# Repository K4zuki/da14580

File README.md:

# da14580
DA14580/murata module PCBs

<br />This work is licensed under a <a rel="license" href="http://creativecommons.org/licenses/by-sa/4.0/">Creative Commons Attribution-ShareAlike 4.0 International License</a>.

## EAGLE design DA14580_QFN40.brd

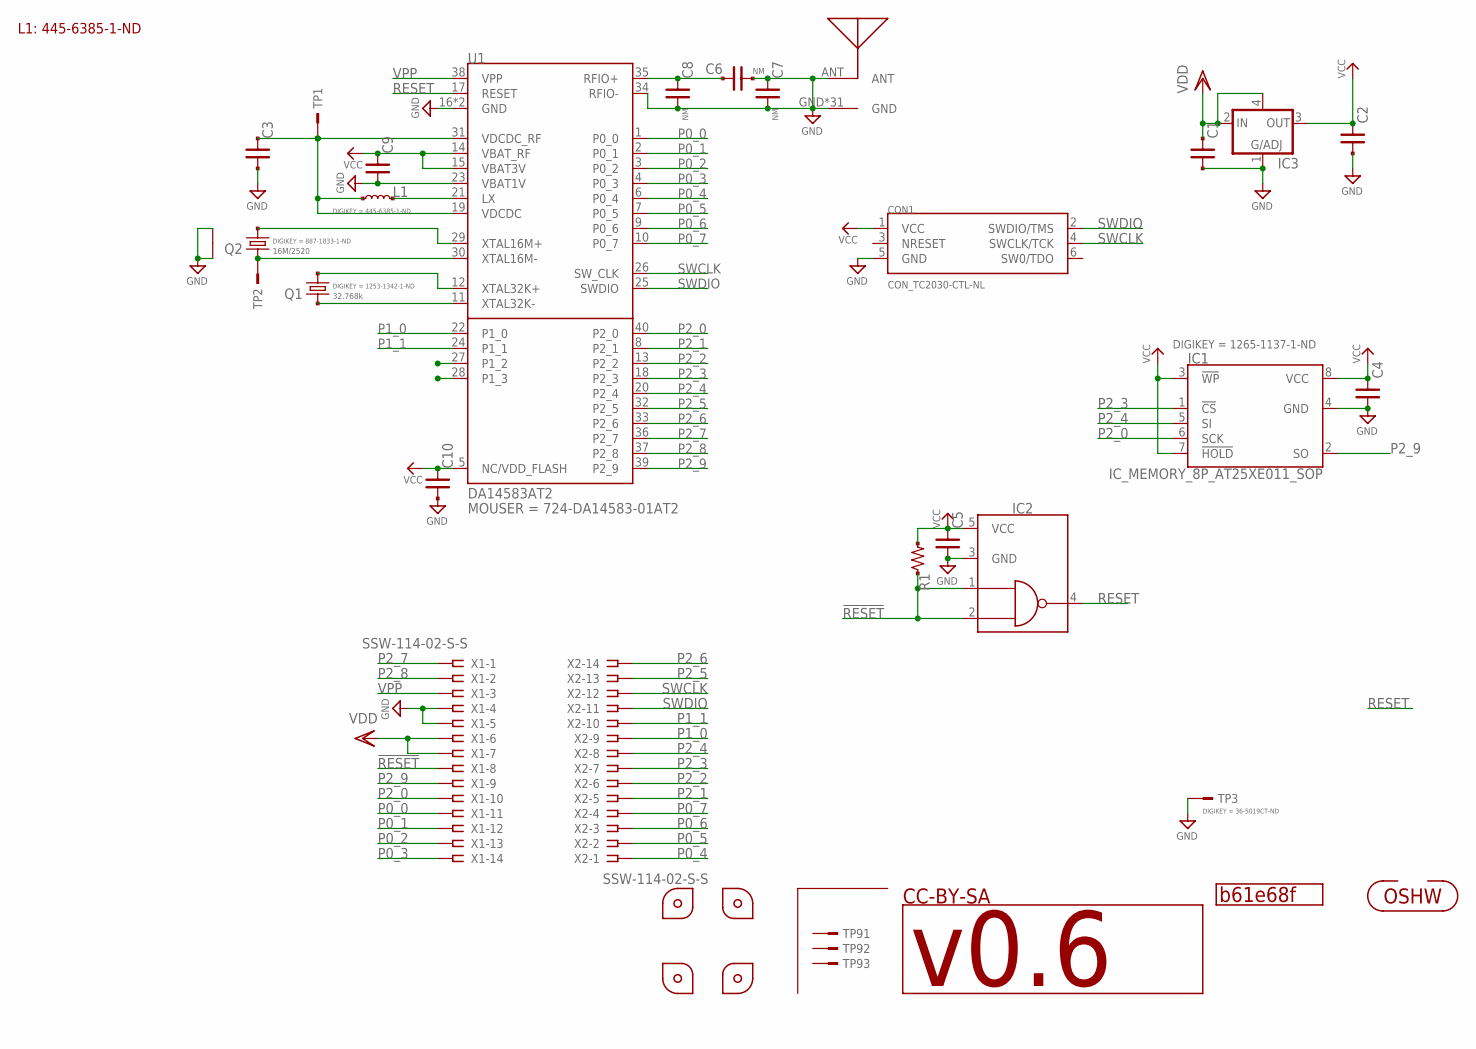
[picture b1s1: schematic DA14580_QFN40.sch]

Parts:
C1, C2, C3, C9: C_SMD_1.0U_1005; C0402
C4, C5, C10: C_SMD_0.1U_1005; C0402
C6, C7, C8: NM; C0402
CON1: CON_TC2030-CTL-NL; CON_TC2030-IDC-NL
GIT1: b61e68f; GIT-REVISION
IC1: IC_MEMORY_8P_AT25XE011_SOP; IC_08_1.27_150MIL
IC2: 74LVC1G00_DRL; SOT50P160X120-5N
IC3: LDO4_3.3_SC82-AB; SOT130P220X135-4N
ICON1: v0.6; ICON_REVISION1.2
L1: INDUCTOR_2.2U_1608; L_1608
P1, P2: PCB_CORNER_NH
P3, P4: PCB_CORNER
Q1: 32.768k; CR_2125
Q2: 16M/2520; CLOCK_2520
R1: R_US_10K_1005; C0402
TP1, TP2: TESTPAD; TP06RECT
TP3: TESTPAD_4020; TP_4020
TP91, TP92, TP93: TESTPAD_F; FIDUCIAL
U1: DA14583AT2; QFN40_0.4P5.0X5.0
U$1: ANT_IFA; ANT_IFA_V2
U$2: ICON_OSHW
X1, X2: SSW-114-02-S-S

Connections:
!RESET!: IC2.1 (1A), IC2.2 (1B), R1.1, X1.8
GND: C1.2, C2.2, C3.2, C4.2, C5.2, C6.2, C7.1, C7.2, C8.2, C9.2, C10.2, CON1.5 (GND), IC1.4 (GND), IC2.3 (GND), IC3.1 (ADJ), Q2.2, Q2.4, TP3.TP, U1.16 (GND), U1.23 (VBAT1V), U1.34 (RFIO-), U1.BP (GND), U$1.ANT, U$1.GND, U$1.GND@1 (GND), U$1.GND@2 (GND), U$1.GND@3 (GND), U$1.GND@4 (GND), U$1.GND@5 (GND), U$1.GND@6 (GND), U$1.GND@7 (GND), U$1.GND@8 (GND), U$1.GND@9 (GND), U$1.GND@10 (GND), U$1.GND@11 (GND), U$1.GND@12 (GND), U$1.GND@13 (GND), U$1.GND@14 (GND), U$1.GND@15 (GND), U$1.GND@16 (GND), U$1.GND@17 (GND), U$1.GND@18 (GND), U$1.GND@19 (GND), U$1.GND@20 (GND), U$1.GND@21 (GND), U$1.GND@22 (GND), U$1.GND@23 (GND), U$1.GND@24 (GND), U$1.GND@25 (GND), U$1.GND@26 (GND), U$1.GND@27 (GND), U$1.GND@28 (GND), U$1.GND@29 (GND), U$1.GND@30 (GND), X1.4, X1.5
unnamed: C6.1, C8.1, U1.35 (RFIO+)
unnamed: L1.2, U1.21 (LX)
unnamed: C3.1, L1.1, TP1.TP, U1.19 (VDCDC), U1.31 (VDCDC_RF)
unnamed: Q1.1, U1.12 (XTAL32K+)
unnamed: Q1.2, U1.11 (XTAL32K-)
unnamed: Q2.1, U1.29 (XTAL16M+)
unnamed: Q2.3 (2), TP2.TP, U1.30 (XTAL16M-)
P0_0: U1.1 (P0_0), X1.11
P0_1: U1.2 (P0_1), X1.12
P0_2: U1.3 (P0_2), X1.13
P0_3: U1.4 (P0_3), X1.14
P0_4: U1.6 (P0_4), X2.1
P0_5: U1.7 (P0_5), X2.2
P0_6: U1.9 (P0_6), X2.3
P0_7: U1.10 (P0_7), X2.4
P1_0: U1.22 (P1_0), X2.9
P1_1: U1.24 (P1_1), X2.10
P1_2: U1.27 (P1_2)
P1_3: U1.28 (P1_3)
P2_0: IC1.6 (SCK), U1.40 (P2_0), X1.10
P2_1: U1.8 (P2_1), X2.5
P2_2: U1.13 (P2_2), X2.6
P2_3: IC1.1 (!CS), U1.18 (P2_3), X2.7
P2_4: IC1.5 (SI), U1.20 (P2_4), X2.8
P2_5: U1.32 (P2_5), X2.13
P2_6: U1.33 (P2_6), X2.14
P2_7: U1.36 (P2_7), X1.1
P2_8: U1.37 (P2_8), X1.2
P2_9: IC1.2 (SO), U1.39 (P2_9), X1.9
RESET: IC2.4 (1Y), U1.17 (RESET)
SWCLK: CON1.4 (SWCLK/TCK), U1.26 (SW_CLK), X2.12
SWDIO: CON1.2 (SWDIO/TMS), U1.25 (SWDIO), X2.11
VCC: C2.1, C4.1, C5.1, C9.1, C10.1, CON1.1 (VCC), IC1.3 (!WP), IC1.7 (!HOLD), IC1.8 (VCC), IC2.5 (VCC), IC3.3 (OUT), R1.2, U1.5 (NC/VDD_FLASH), U1.14 (VBAT_RF), U1.15 (VBAT3V)
VDD: C1.1, IC3.2 (IN), IC3.4 (OUT/EN/NC), X1.6, X1.7
VPP: U1.38 (VPP), X1.3

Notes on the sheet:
L1: 445-6385-1-ND
CC-BY-SA

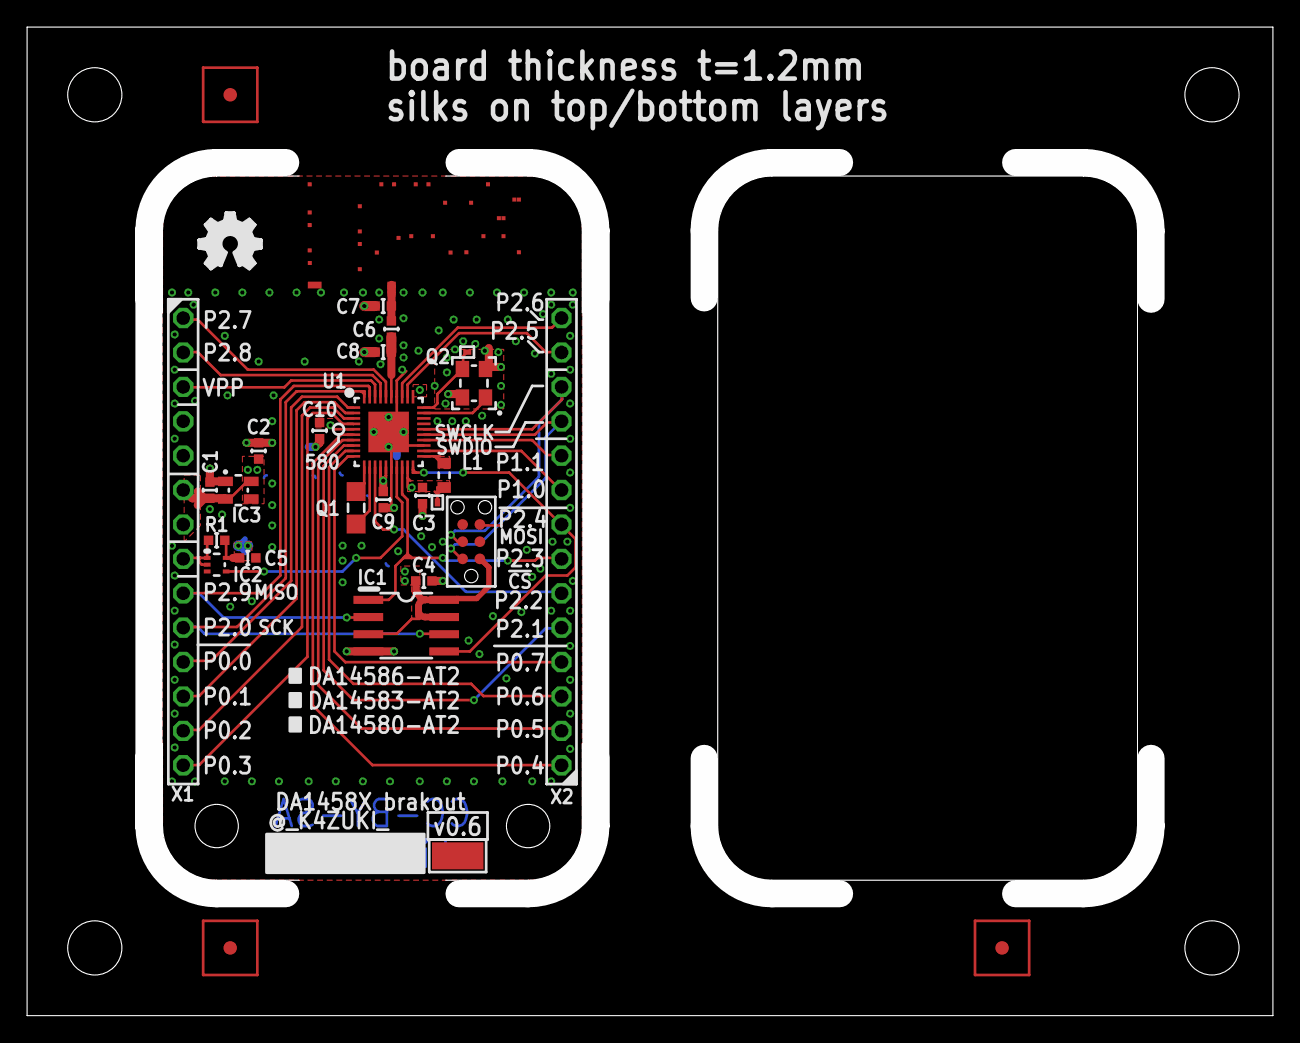
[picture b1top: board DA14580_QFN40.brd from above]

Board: 2 copper layers, 92.0 x 73.0 mm, 35 parts (0 on the bottom side), 35 nets.

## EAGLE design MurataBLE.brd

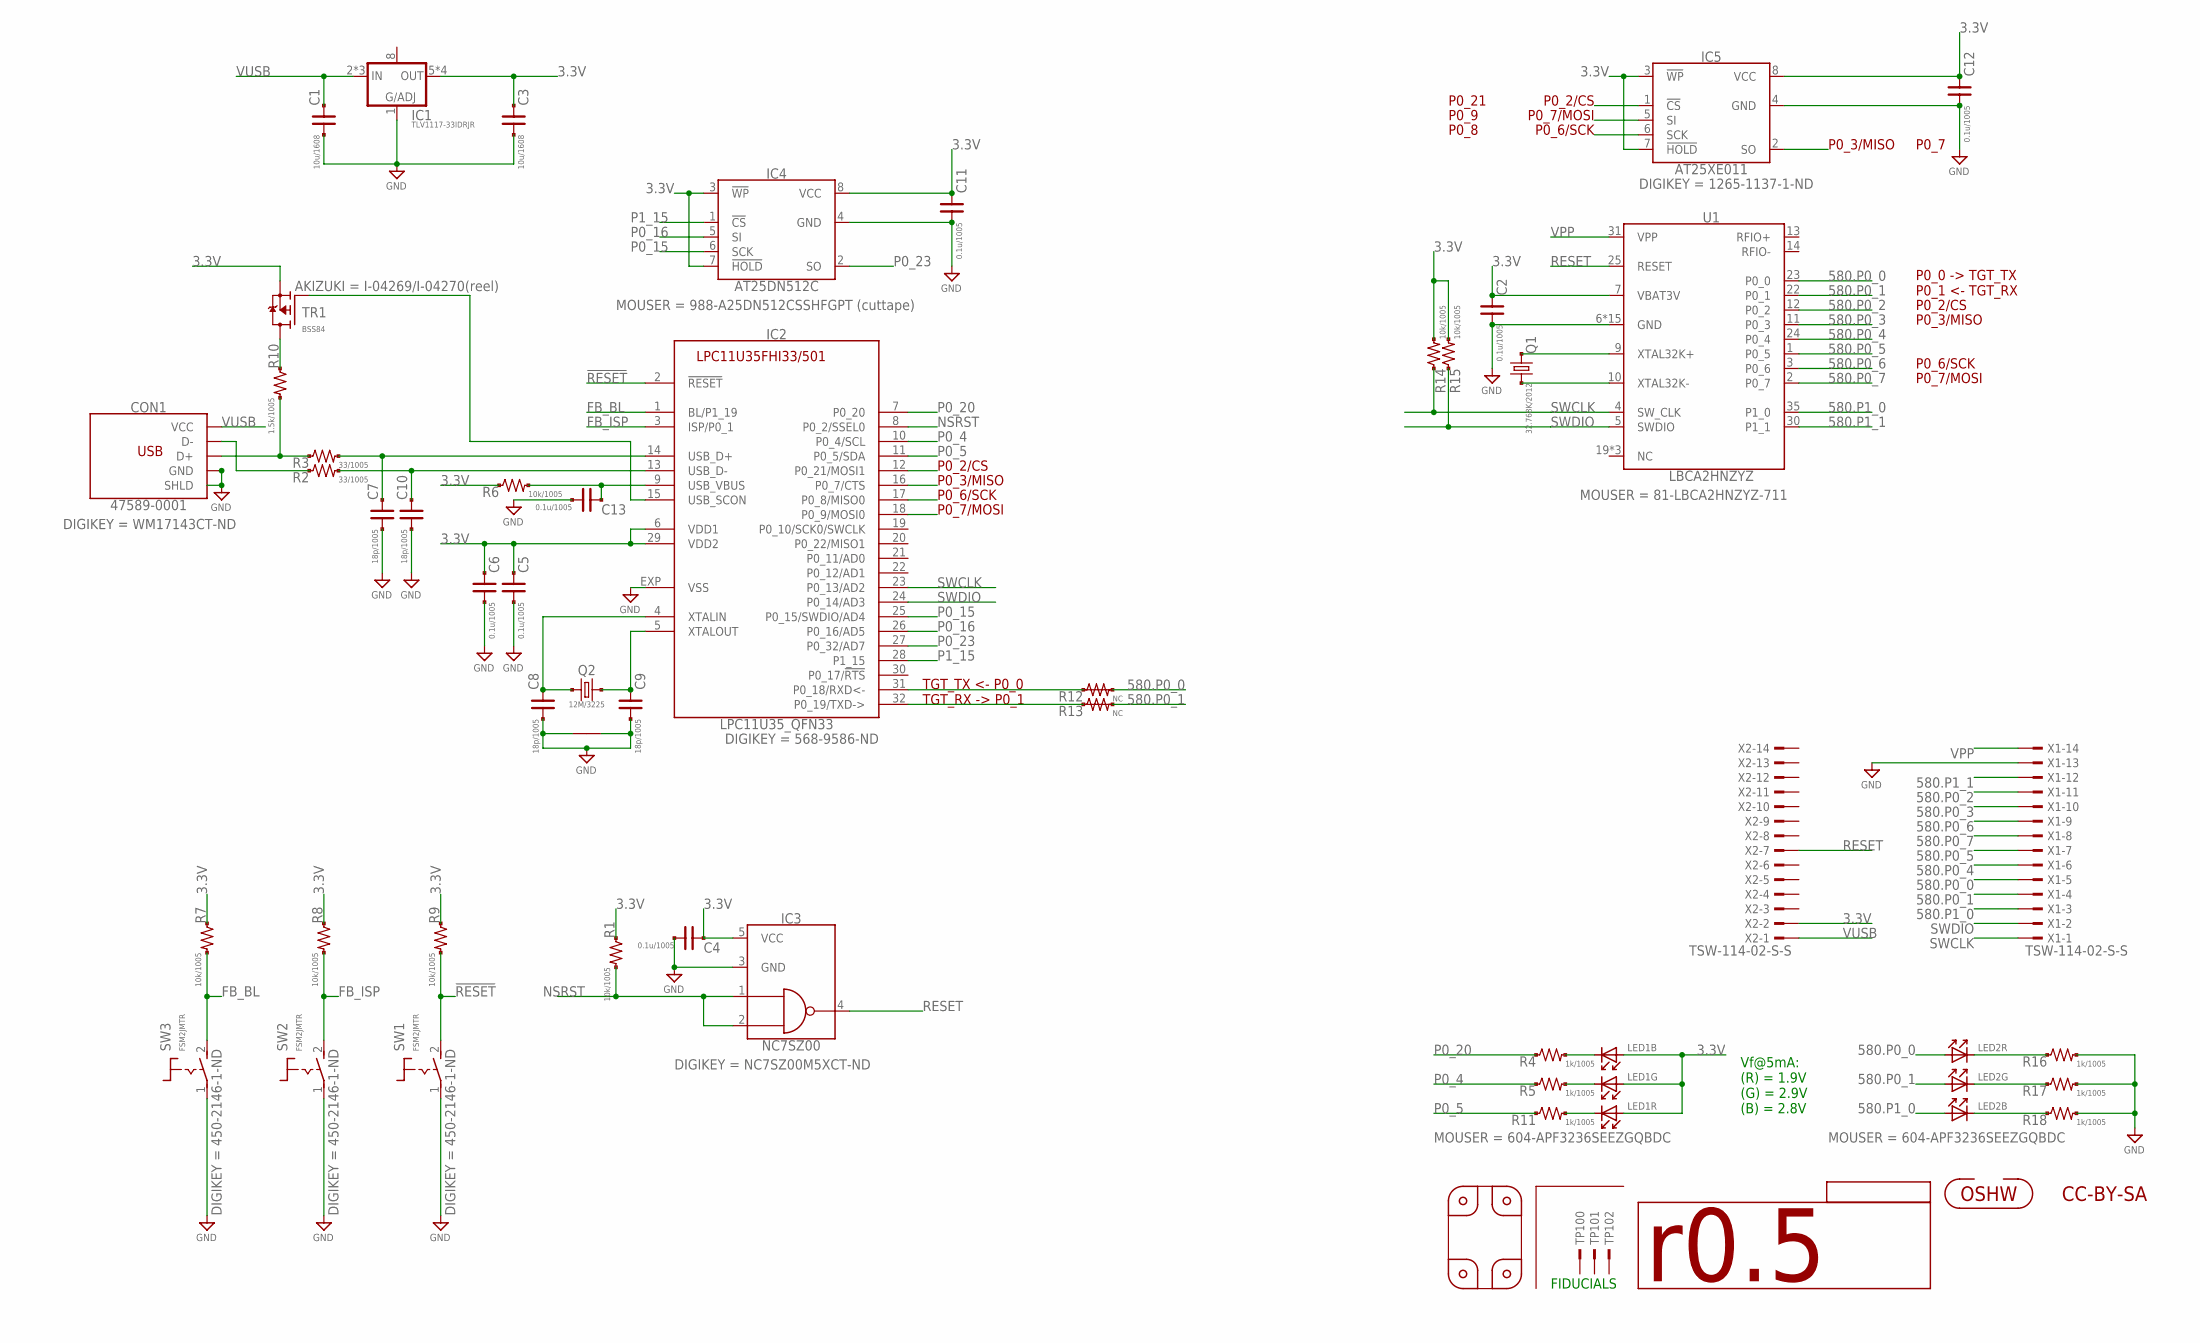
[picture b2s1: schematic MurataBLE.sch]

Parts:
C1, C3: 10u/1608; CR_1608
C2, C4, C5, C6, C11, C12, C13: 0.1u/1005; C0402
C7, C8, C9, C10: 18p/1005; C0402
CON1: 47589-0001; CON_USB_47589-0001MOLEX
GIT1: GIT-REVISION
IC1: TLV1117-33IDRJR; DFN80P410X410_8N
IC2: LPC11U35_QFN33; HVQFN33
IC3: NC7SZ00; SOT95P280X145-5N
IC4: AT25DN512C; IC_08_1.27_150MIL
IC5: AT25XE011; IC_08_1.27_150MIL
ICON1: r0.5; ICON_REVISION1.2
ICON2: NC; ICON_OSHW
LED1, LED2: LED_3SEG; LED_3SEG_SMD
P1, P2, P3, P4: NC; PCB_CORNER_NH
Q1: 32.768K/2012; CR_2125
Q2: 12M/3225; CLOCK_3225
R1, R6, R7, R8, R9, R14, R15: 10k/1005; C0402
R2, R3: 33/1005; C0402
R4, R5, R11, R16, R17, R18: 1k/1005; C0402
R10: 1.5k/1005; C0402
R12, R13: NC; R0402SHORT
SW1, SW2, SW3: FSM2JMTR; SW_TACTSW_FSM2JMTR
TP100, TP101, TP102: NC; FIDUCIAL
TR1: BSS84; SOT95P300X140-3N
U1: LBCA2HNZYZ; IC_MURATA_LBCA2HNZYZ-711
X1, X2: TSW-114-02-S-S; TSW-114-07-F-S

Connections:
3.3V: C2.1, C3.1, C4.1, C5.1, C6.1, C11.1, C12.1, IC1.5 (OUT), IC1.6 (OUT), IC1.7 (OUT), IC1.EP (OUT), IC2.6 (VDD1), IC2.29 (VDD2), IC3.5 (VCC), IC4.3 (!WP), IC4.7 (!HOLD), IC4.8 (VCC), IC5.3 (!WP), IC5.7 (!HOLD), IC5.8 (VCC), LED1.4 (A), LED1.5 (A), LED1.6 (A), R1.1, R6.1, R7.1, R8.1, R9.1, R14.2, R15.2, TR1.2 (S), U1.7 (VBAT3V), X2.2
580.P0_0: LED2.4 (A), R12.3 (2), U1.23 (P0_0), X1.5
580.P0_1: LED2.5 (A), R13.3 (2), U1.22 (P0_1), X1.4
580.P0_2: IC2.12 (P0_21/MOSI1), IC5.1 (!CS), U1.12 (P0_2), X1.11
580.P0_3: IC2.16 (P0_7/CTS), IC5.2 (SO), U1.11 (P0_3), X1.10
580.P0_4: U1.24 (P0_4), X1.6
580.P0_5: U1.1 (P0_5), X1.7
580.P0_6: IC2.17 (P0_8/MISO0), IC5.6 (SCK), U1.3 (P0_6), X1.9
580.P0_7: IC2.18 (P0_9/MOSI0), IC5.5 (SI), U1.2 (P0_7), X1.8
580.P1_0: LED2.6 (A), U1.35 (P1_0), X1.3
580.P1_1: U1.30 (P1_1), X1.12
!RESET!: IC2.2 (!RESET!), R9.2, SW1.2 (S)
FB_BL: IC2.1 (BL/P1_19), R7.2, SW3.2 (S)
FB_ISP: IC2.3 (ISP/P0_1), R8.2, SW2.2 (S)
GND: C1.2, C2.2, C3.2, C4.2, C5.2, C6.2, C7.2, C8.2, C9.2, C10.2, C11.2, C12.2, C13.2, CON1.5 (GND), CON1.SHD (SHLD), CON1.SHD$1 (SHLD), CON1.SHD$2 (SHLD), CON1.SHD$3 (SHLD), CON1.SHD$4 (SHLD), CON1.SHD$5 (SHLD), CON1.SHD$6 (SHLD), CON1.SHD$7 (SHLD), IC1.1 (ADJ), IC2.EXP (VSS), IC3.3 (GND), IC4.4 (GND), IC5.4 (GND), Q2.2, Q2.4, R16.2, R17.2, R18.2, SW1.1, SW2.1, SW3.1, U1.6 (GND), U1.8 (GND), U1.15 (GND), U1.16 (GND), U1.17 (GND), U1.18 (GND), U1.20 (GND), U1.21 (GND), U1.26 (GND), U1.27 (GND), U1.28 (GND), U1.29 (GND), U1.32 (GND), U1.33 (GND), U1.34 (GND), X1.13
unnamed: Q1.1, U1.9 (XTAL32K+)
unnamed: Q1.2, U1.10 (XTAL32K-)
unnamed: C13.1, IC2.9 (USB_VBUS), R6.2
unnamed: R10.1, TR1.3 (D)
unnamed: IC2.15 (USB_SCON), TR1.1 (G)
unnamed: LED1.1 (K), R11.2
unnamed: LED1.2 (K), R5.2
unnamed: LED1.3 (K), R4.2
unnamed: LED2.3 (K), R18.1
unnamed: LED2.2 (K), R17.1
unnamed: LED2.1 (K), R16.1
unnamed: C8.1, IC2.4 (XTALIN), Q2.1
unnamed: C9.1, IC2.5 (XTALOUT), Q2.3 (2)
unnamed: C7.1, IC2.14 (USB_D+), R3.2
unnamed: CON1.3 (D+), R3.1, R10.2
unnamed: CON1.2 (D-), R2.1
unnamed: C10.1, IC2.13 (USB_D-), R2.2
NSRST: IC2.8 (P0_2/SSEL0), IC3.1 (1A), IC3.2 (1B), R1.2
P0_4: IC2.10 (P0_4/SCL), R5.1
P0_5: IC2.11 (P0_5/SDA), R11.1
P0_15: IC2.25 (P0_15/SWDIO/AD4), IC4.6 (SCK)
P0_16: IC2.26 (P0_16/AD5), IC4.5 (SI)
P0_20: IC2.7 (P0_20), R4.1
P0_23: IC2.27 (P0_32/AD7), IC4.2 (SO)
P1_15: IC2.28 (P1_15), IC4.1 (!CS)
RESET: IC3.4 (1Y), U1.25 (RESET), X2.7
SWCLK: IC2.23 (P0_13/AD2), R14.1, U1.4 (SW_CLK), X1.1
SWDIO: IC2.24 (P0_14/AD3), R15.1, U1.5 (SWDIO), X1.2
TGT_RX: IC2.32 (P0_19/TXD->), R13.1, R13.2 (1)
TGT_TX: IC2.31 (P0_18/RXD<-), R12.1, R12.2 (1)
VPP: U1.31 (VPP), X1.14
VUSB: C1.1, CON1.1 (VCC), IC1.2 (IN), IC1.3 (IN), IC1.4 (IN), X2.1

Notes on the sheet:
Vf@5mA: (R) = 1.9V (G) = 2.9V (B) = 2.8V
TGT_TX <- P0_0 TGT_RX -> P0_1
P0_0 -> TGT_TX P0_1 <- TGT_RX
CC-BY-SA
FIDUCIALS
P0_2/CS
P0_7/MOSI
P0_3/MISO
P0_6/SCK
P0_21
P0_9
P0_8
P0_7

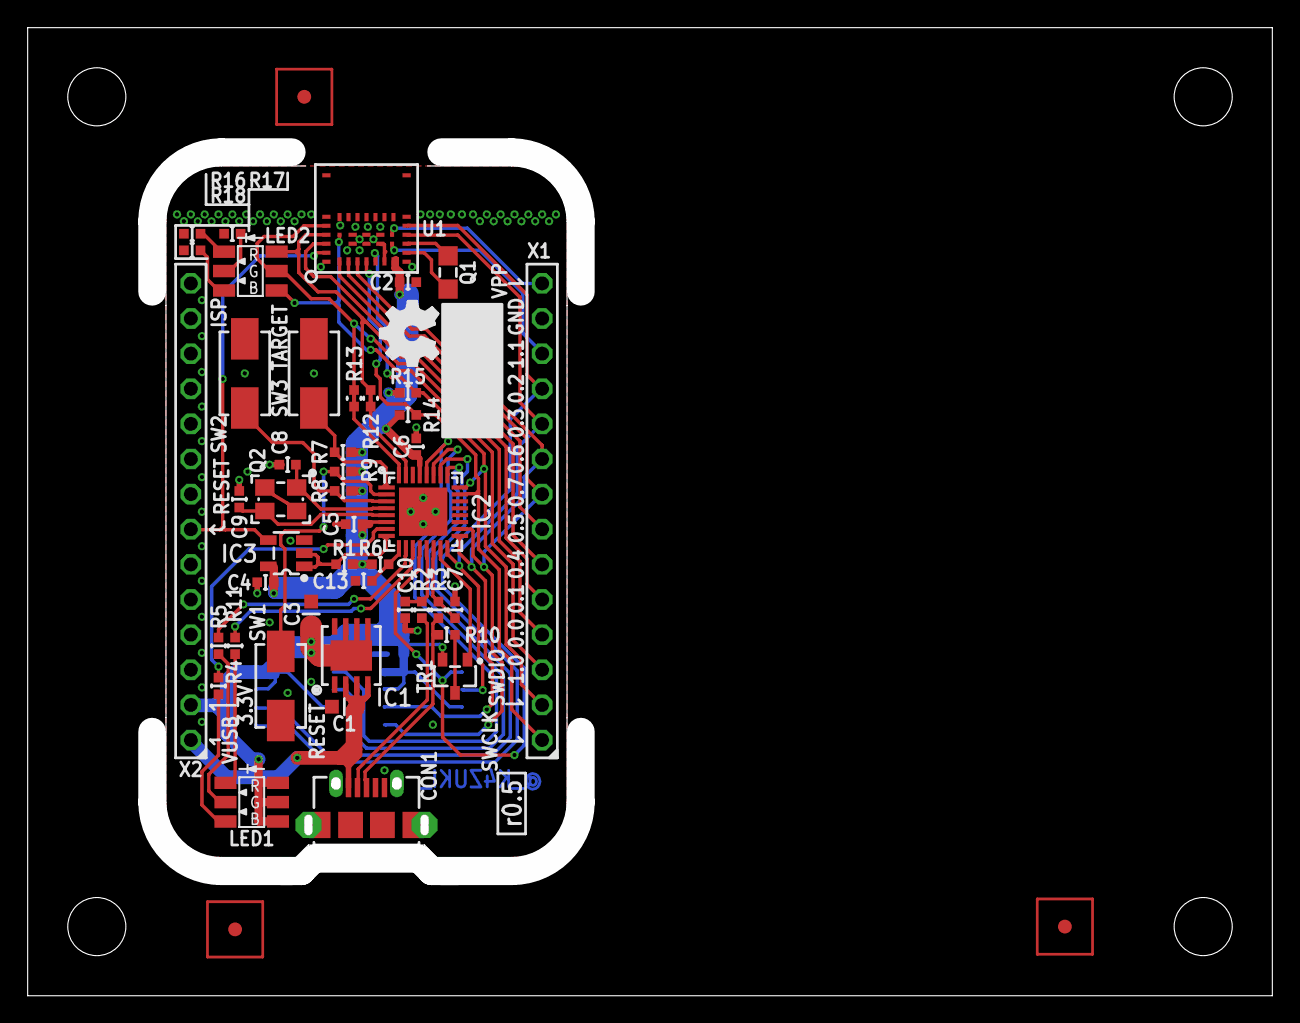
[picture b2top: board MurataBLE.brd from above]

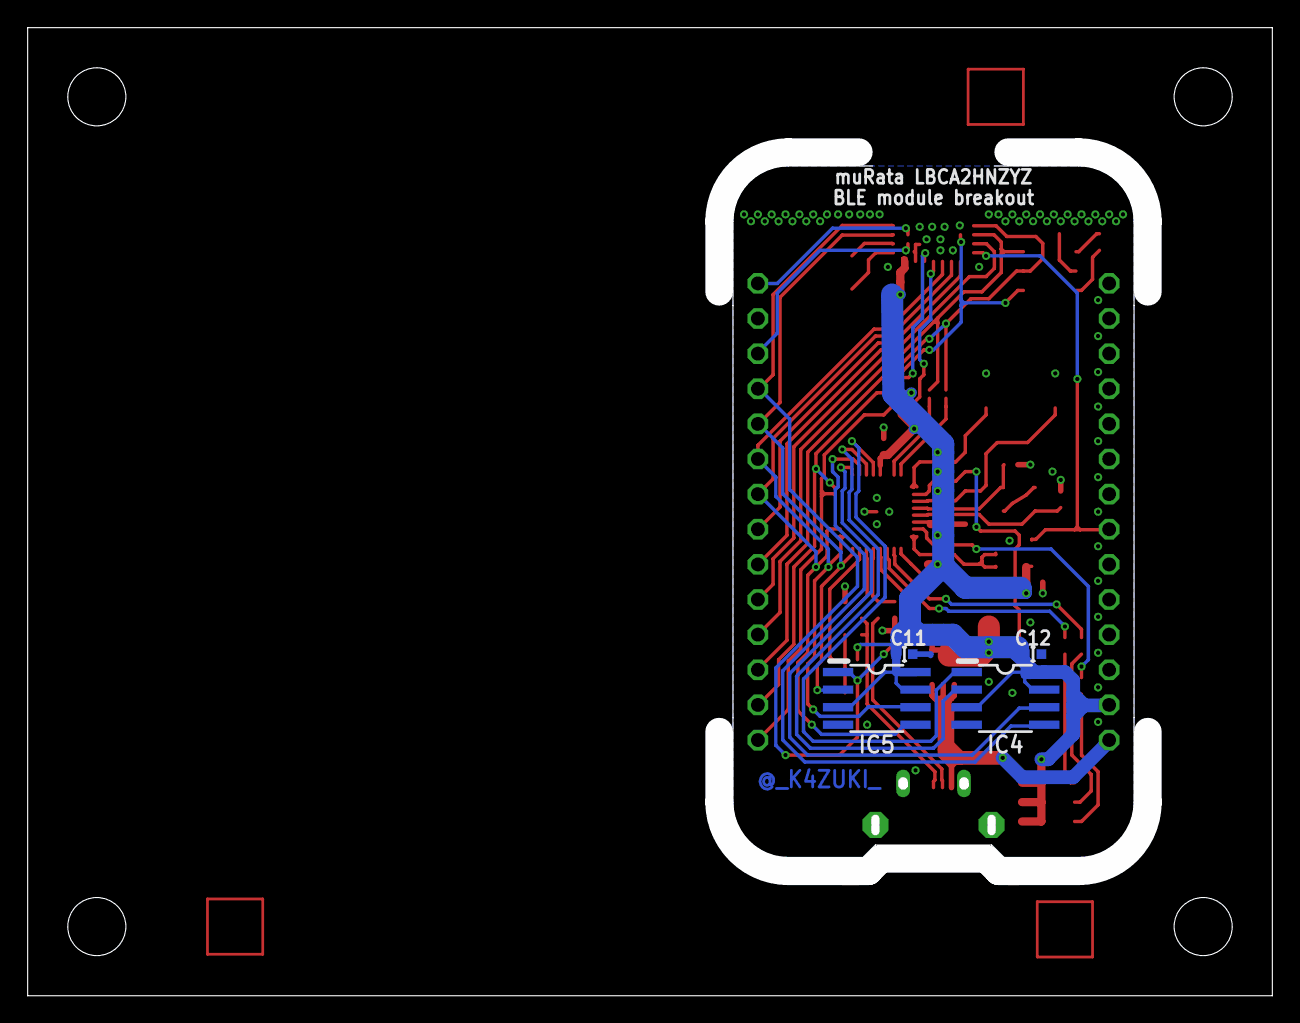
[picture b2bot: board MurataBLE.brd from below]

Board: 2 copper layers, 90.0 x 70.0 mm, 58 parts (4 on the bottom side), 47 nets.

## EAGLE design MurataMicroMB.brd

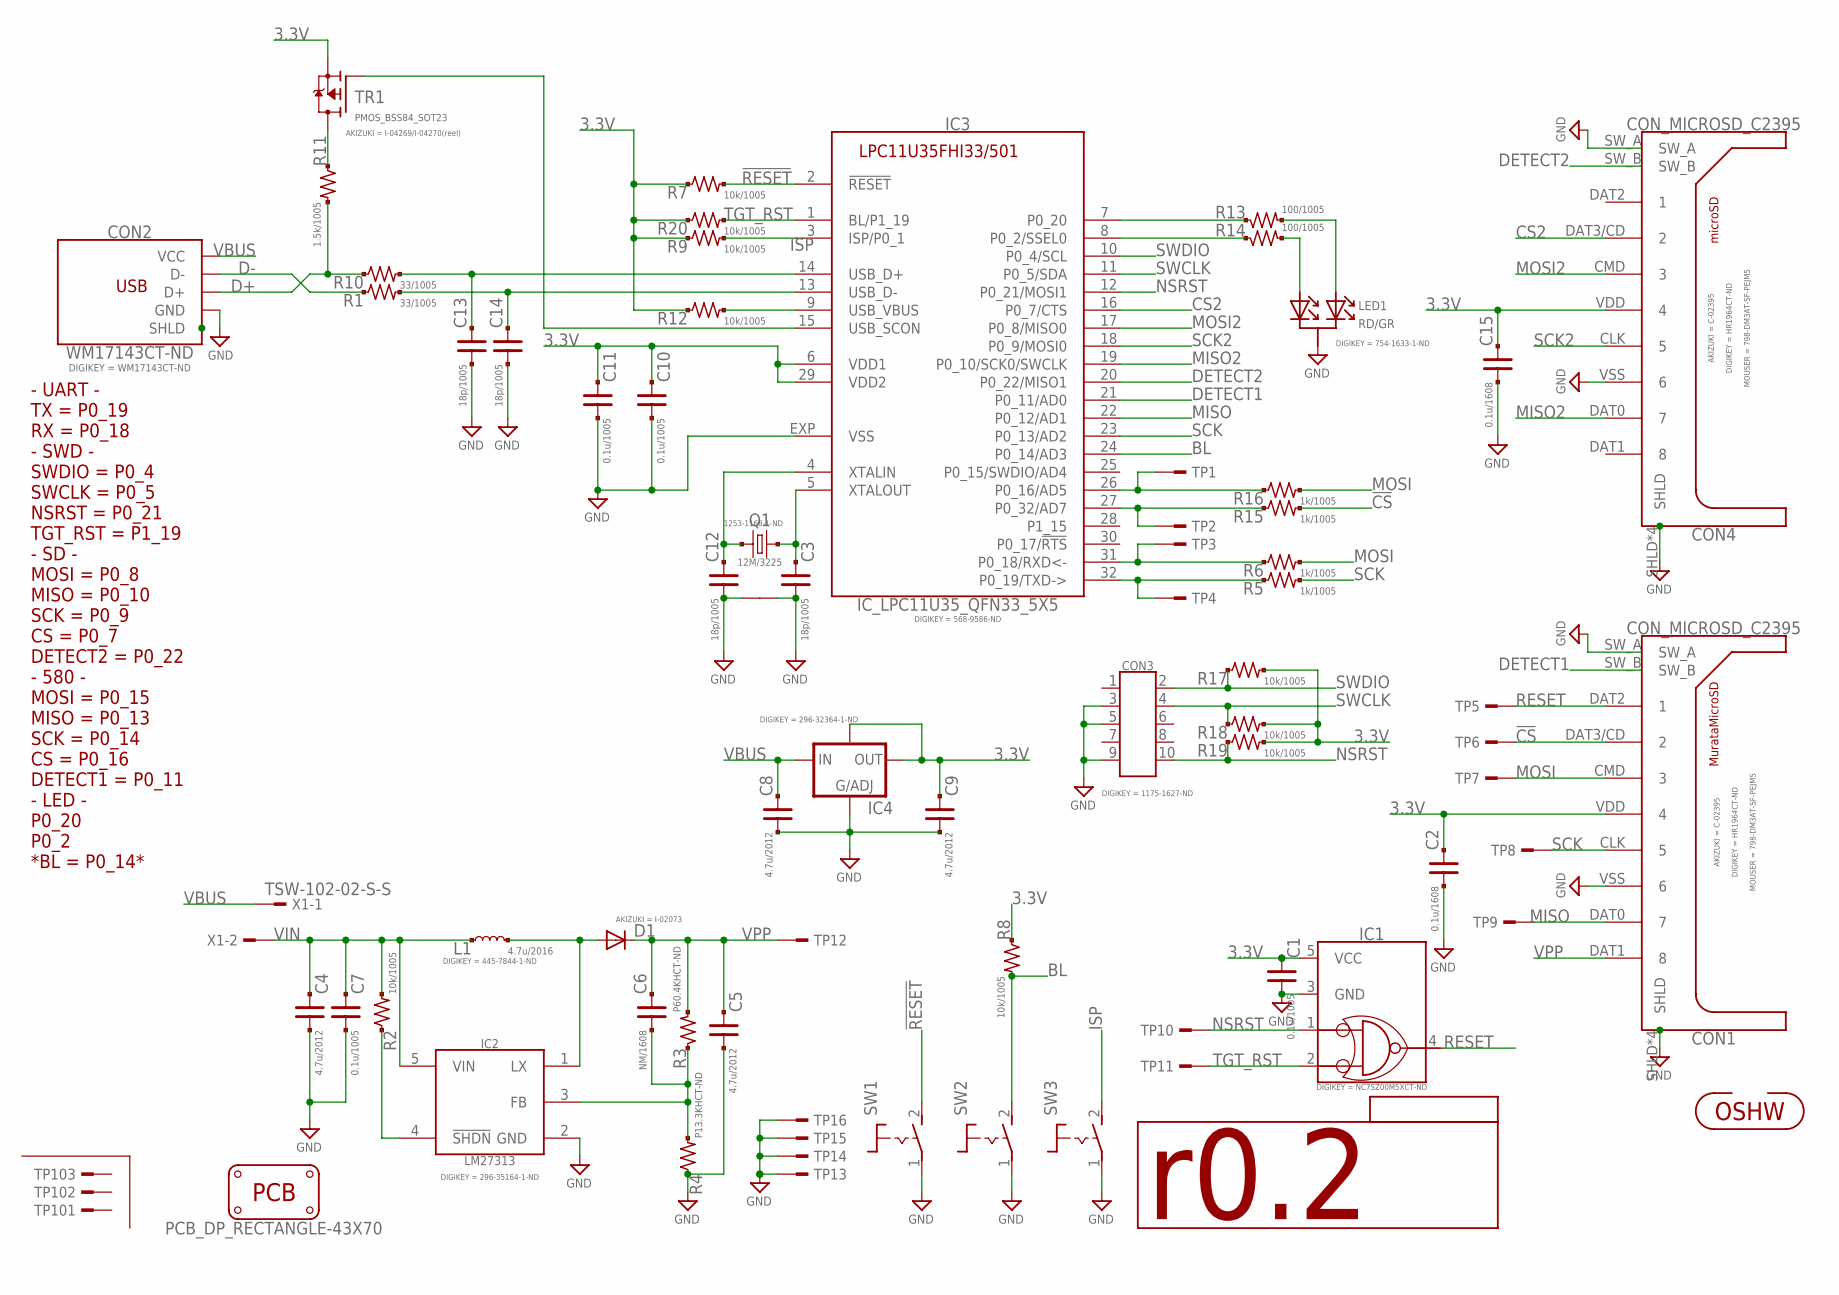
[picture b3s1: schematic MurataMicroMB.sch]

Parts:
C1, C7, C10, C11: 0.1u/1005; C0402
C2, C15: 0.1u/1608; CR_1608
C3, C12, C13, C14: 18p/1005; C0402
C4, C5, C8, C9: 4.7u/2012; CR_2125
C6: NM/1608; CR_1608
CON1, CON4: CON_MICROSD_C2395
CON2: WM17143CT-ND; CON_USB_47589-0001MOLEX
CON3: CON_MIL_10_ARM; CON_CORESIGHT10_1175-1627-ND
D1: 40V2A; DIODE_2125
GIT1: GIT-REVISION
IC1: IC_TTL_SINGLE_74_00_SOT23; SOT95P280X145-5N
IC2: LM27313; SOT95P280X145-5N
IC3: IC_LPC11U35_QFN33_5X5; HVQFN33
IC4: LDO4_3.3_DRJ; DFN80P410X410_8N
ICON1: r0.2; ICON_REVISION2.0
L1: 4.7u/2016; L_2016
LED1: RD/GR; SOT105P300X130-3N
PCB1: PCB_DP_RECTANGLE-43X70; DP7043_V1
Q1: 12M/3225; CLOCK_3225
R1, R10: 33/1005; C0402
R2, R7, R8, R9, R12, R17, R18, R19, R20: 10k/1005; C0402
R3: P60.4KHCT-ND; R_1608_PADPAD
R4: P13.3KHCT-ND; R_1608_PADPAD
R5, R6, R15, R16: 1k/1005; C0402
R11: 1.5k/1005; C0402
R13, R14: 100/1005; C0402
SW1, SW2, SW3: TACTSW2_FSM2JMTR; SW_TACTSW_FSM2JMTR
TP1, TP2, TP3, TP4: TESTPAD_1608; TP_1608
TP5, TP6, TP7, TP8, TP9, TP10, TP11, TP12: TESTPAD; TP06RECT
TP13, TP14, TP15, TP16: TESTPAD_4020; TP_4020
TP101, TP102, TP103: TESTPAD_F; FIDUCIAL
TR1: PMOS_BSS84_SOT23; SOT95P300X140-3N
U$1: ICON_OSHW
X1: TSW-102-02-S-S

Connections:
3.3V: C1.1, C2.1, C9.1, C10.1, C11.1, C15.1, CON1.VDD (4), CON4.VDD (4), IC1.5 (VCC), IC3.6 (VDD1), IC3.29 (VDD2), IC4.5 (OUT), IC4.6 (OUT), IC4.7 (OUT), IC4.8 (OUT/EN/NC), IC4.EP (OUT), R7.1, R8.1, R9.1, R12.1, R17.2, R18.2, R19.2, R20.1, TR1.2 (S)
!CS!: CON1.DAT3/CD (2), R15.2, TP6.TP
!RESET!: IC3.2 (!RESET!), R7.2, SW1.2 (S)
BL: IC3.24 (P0_14/AD3), R8.2, SW2.2 (S)
CS2: CON4.DAT3/CD (2), IC3.16 (P0_7/CTS)
D+: CON2.3 (D+), R10.1, R11.2
D-: CON2.2 (D-), R1.1
DETECT1: CON1.SW_B, IC3.21 (P0_11/AD0)
DETECT2: CON4.SW_B, IC3.20 (P0_22/MISO1)
GND: C1.2, C2.2, C3.2, C4.2, C5.2, C7.2, C8.2, C9.2, C10.2, C11.2, C12.2, C13.2, C14.2, C15.2, CON1.SHLD, CON1.SHLD@2 (SHLD), CON1.SHLD@3 (SHLD), CON1.SHLD@4 (SHLD), CON1.SW_A, CON1.VSS (6), CON2.5 (GND), CON3.3, CON3.5, CON3.9, CON4.SHLD, CON4.SHLD@2 (SHLD), CON4.SHLD@3 (SHLD), CON4.SHLD@4 (SHLD), CON4.SW_A, CON4.VSS (6), IC1.3 (GND), IC2.2 (GND), IC3.EXP (VSS), IC4.1 (ADJ), LED1.3 (K1), Q1.2, Q1.4, R4.1, SW1.1, SW2.1, SW3.1, TP13.TP, TP14.TP, TP15.TP, TP16.TP
ISP: IC3.3 (ISP/P0_1), R9.2, SW3.2 (S)
MISO: CON1.DAT0 (7), IC3.22 (P0_12/AD1), TP9.TP
MISO2: CON4.DAT0 (7), IC3.19 (P0_10/SCK0/SWCLK)
MOSI: CON1.CMD (3), R6.2, R16.2, TP7.TP
MOSI2: CON4.CMD (3), IC3.17 (P0_8/MISO0)
unnamed: IC3.8 (P0_2/SSEL0), R14.1
unnamed: R11.1, TR1.3 (D)
unnamed: CON2.SHD (SHLD), CON2.SHD$1 (SHLD), CON2.SHD$2 (SHLD), CON2.SHD$3 (SHLD), CON2.SHD$4 (SHLD), CON2.SHD$5 (SHLD), CON2.SHD$6 (SHLD), CON2.SHD$7 (SHLD)
unnamed: C12.1, IC3.4 (XTALIN), Q1.1
unnamed: IC3.31 (P0_18/RXD<-), R6.1, TP3.TP
unnamed: D1.A, IC2.1 (LX), L1.2
unnamed: IC2.4 (!SHDN!), R2.1
unnamed: IC3.32 (P0_19/TXD->), R5.1, TP4.TP
unnamed: C6.2, IC2.3 (FB), R3.1, R4.2
unnamed: C3.1, IC3.5 (XTALOUT), Q1.3 (2)
unnamed: IC3.15 (USB_SCON), TR1.1 (G)
unnamed: IC3.9 (USB_VBUS), R12.2
unnamed: IC3.7 (P0_20), R13.1
unnamed: LED1.2 (A2), R13.2
unnamed: LED1.1 (A1), R14.2
unnamed: IC3.26 (P0_16/AD5), R16.1, TP1.TP
unnamed: IC3.27 (P0_32/AD7), R15.1, TP2.TP
unnamed: C13.1, IC3.14 (USB_D+), R10.2
unnamed: C14.1, IC3.13 (USB_D-), R1.2
NSRST: CON3.10, IC1.1 (1A), IC3.12 (P0_21/MOSI1), R19.1, TP10.TP
RESET: CON1.DAT2 (1), IC1.4 (1Y), TP5.TP
SCK: CON1.CLK (5), IC3.23 (P0_13/AD2), R5.2, TP8.TP
SCK2: CON4.CLK (5), IC3.18 (P0_9/MOSI0)
SWCLK: CON3.4, IC3.11 (P0_5/SDA), R18.1
SWDIO: CON3.2, IC3.10 (P0_4/SCL), R17.1
TGT_RST: IC1.2 (1B), IC3.1 (BL/P1_19), R20.2, TP11.TP
VBUS: C8.1, CON2.1 (VCC), IC4.2 (IN), IC4.3 (IN), IC4.4 (IN), X1.1
VIN: C4.1, C7.1, IC2.5 (VIN), L1.1, R2.2, X1.2
VPP: C5.1, C6.1, CON1.DAT1 (8), D1.K (C), R3.2, TP12.TP

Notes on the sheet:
MurataMicroSD
microSD
- UART - TX = P0_19 RX = P0_18 - SWD - SWDIO = P0_4 SWCLK = P0_5 NSRST = P0_21 TGT_RST = P1_19 - SD - MOSI = P0_8 MISO = P0_10 SCK = P0_9 CS = P0_7 DETECT2 = P0_22 - 580 - MOSI = P0_15 MISO = P0_13 SCK = P0_14 CS = P0_16 DETECT1 = P0_11 - LED - P0_20 P0_2 *BL = P0_14*

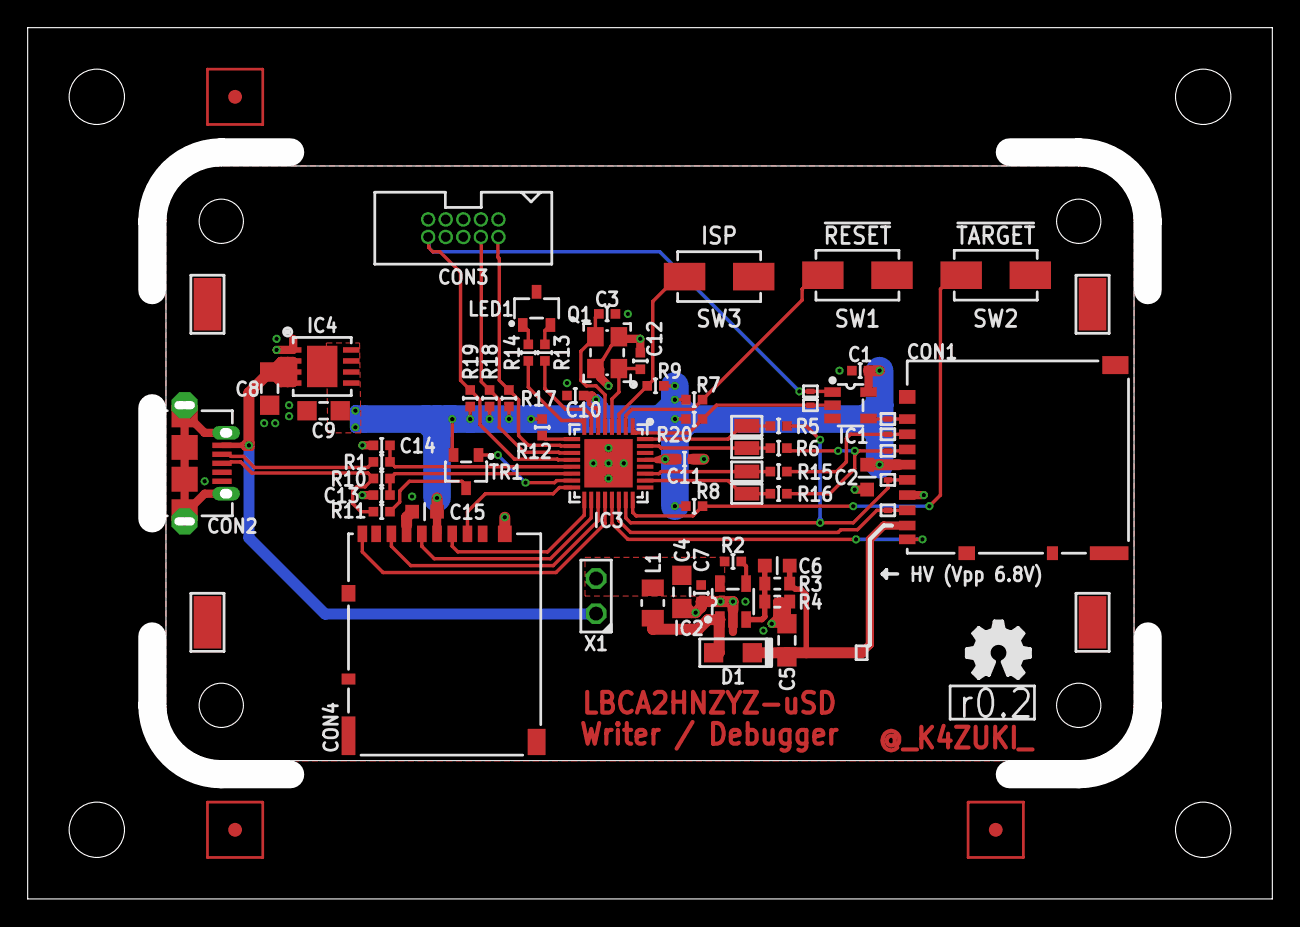
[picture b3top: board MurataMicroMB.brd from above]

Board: 2 copper layers, 90.0 x 63.0 mm, 75 parts (0 on the bottom side), 44 nets.

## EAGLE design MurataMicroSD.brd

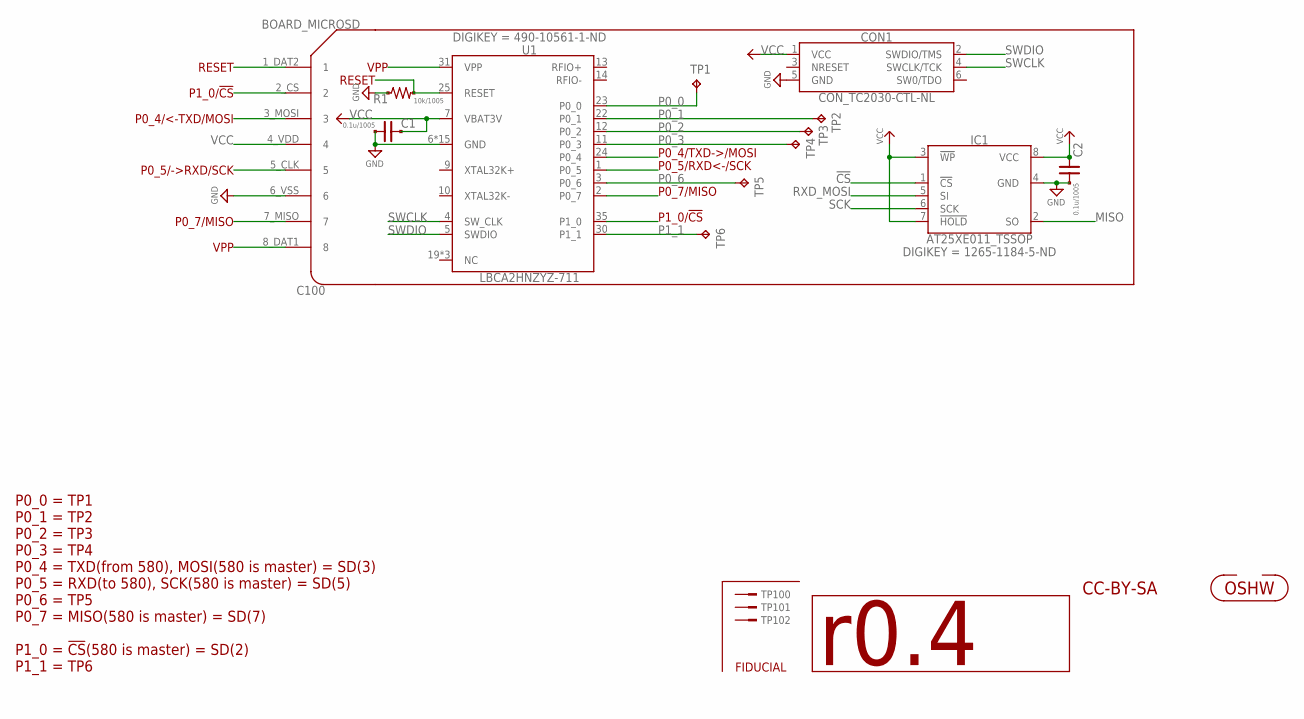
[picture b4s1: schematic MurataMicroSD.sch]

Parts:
C1, C2: 0.1u/1005; C0402
C100: BOARD_MICROSD
CON1: CON_TC2030-CTL-NL; CON_TC2030-IDC-NL
IC1: AT25XE011_TSSOP; IC_08_0.65_160MIL
ICON1: r0.4; ICON_REVISION1.2
R1: 10k/1005; C0402
TP1, TP2, TP3, TP4, TP5, TP6: TPTP08R; TP08R
TP100, TP101, TP102: TESTPAD_F; FIDUCIAL
U1: LBCA2HNZYZ-711; IC_MURATA_LBCA2HNZYZ-711
U$1: ICON_OSHW

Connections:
!CS!: C100.2_CS (2), IC1.1 (!CS), U1.35 (P1_0)
GND: C1.2, C2.2, C100.6_VSS (6), CON1.5 (GND), IC1.4 (GND), R1.1, U1.6 (GND), U1.8 (GND), U1.15 (GND), U1.16 (GND), U1.17 (GND), U1.18 (GND), U1.20 (GND), U1.21 (GND), U1.26 (GND), U1.27 (GND), U1.28 (GND), U1.29 (GND), U1.32 (GND), U1.33 (GND), U1.34 (GND)
MISO: C100.7_MISO (7), IC1.2 (SO), U1.2 (P0_7)
unnamed: C100.1_DAT2 (1), R1.2, U1.25 (RESET)
P0_0: TP1.TP, U1.23 (P0_0)
P0_1: TP2.TP, U1.22 (P0_1)
P0_2: TP3.TP, U1.12 (P0_2)
P0_3: TP4.TP, U1.11 (P0_3)
P0_6: TP5.TP, U1.3 (P0_6)
P1_1: TP6.TP, U1.30 (P1_1)
RXD_MOSI: C100.3_MOSI (3), IC1.5 (SI), U1.24 (P0_4)
SCK: C100.5_CLK (5), IC1.6 (SCK), U1.1 (P0_5)
SWCLK: CON1.4 (SWCLK/TCK), U1.4 (SW_CLK)
SWDIO: CON1.2 (SWDIO/TMS), U1.5 (SWDIO)
VCC: C1.1, C2.1, C100.4_VDD (4), CON1.1 (VCC), IC1.3 (!WP), IC1.7 (!HOLD), IC1.8 (VCC), U1.7 (VBAT3V)
VPP: C100.8_DAT1 (8), U1.31 (VPP)

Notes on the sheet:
FIDUCIAL
P1_0/!CS!
P0_4/TXD->/MOSI
P0_5/RXD<-/SCK
RESET
P0_5/->RXD/SCK
P0_4/<-TXD/MOSI
P0_7/MISO
CC-BY-SA
VPP
P0_0 = TP1 P0_1 = TP2 P0_2 = TP3 P0_3 = TP4 P0_4 = TXD(from 580), MOSI(580 is master) = SD(3) P0_5 = RXD(to 580), SCK(580 is master) = SD(5) P0_6 = TP5 P0_7 = MISO(580 is master) = SD(7) P1_0 = !CS!(580 is master) = SD(2) P1_1 = TP6

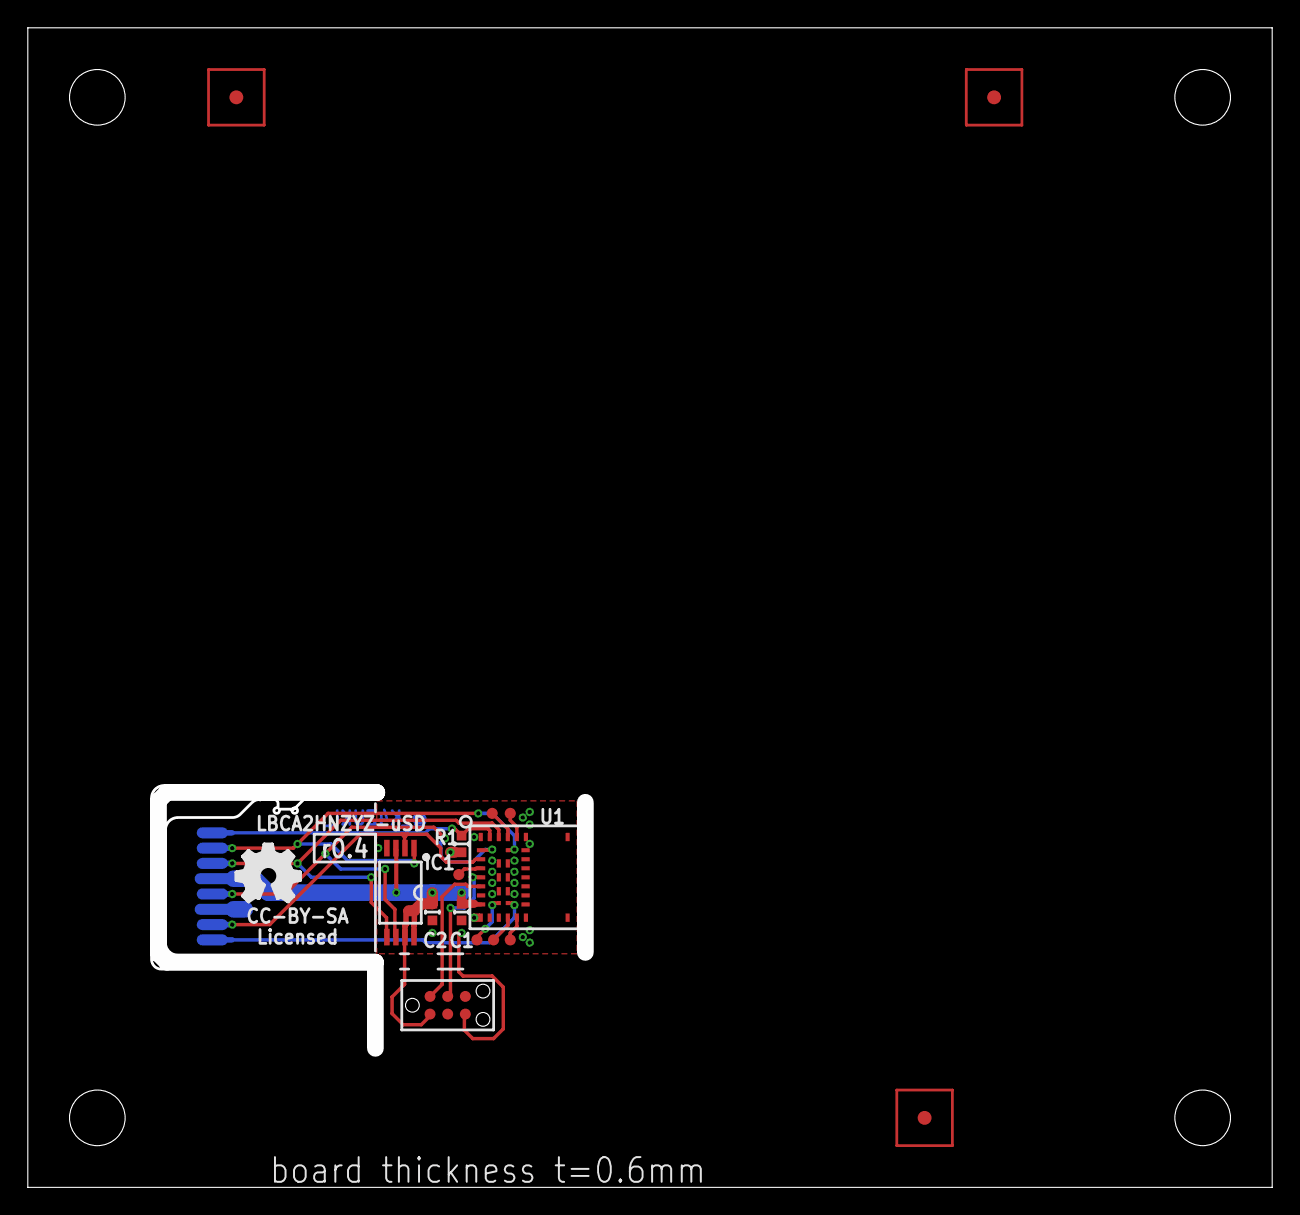
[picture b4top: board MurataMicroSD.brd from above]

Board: 2 copper layers, 89.5 x 83.4 mm, 18 parts (1 on the bottom side), 16 nets.

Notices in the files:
DA14580_QFN40_0v5_P.brd:
CC-BY-SA Licensed
